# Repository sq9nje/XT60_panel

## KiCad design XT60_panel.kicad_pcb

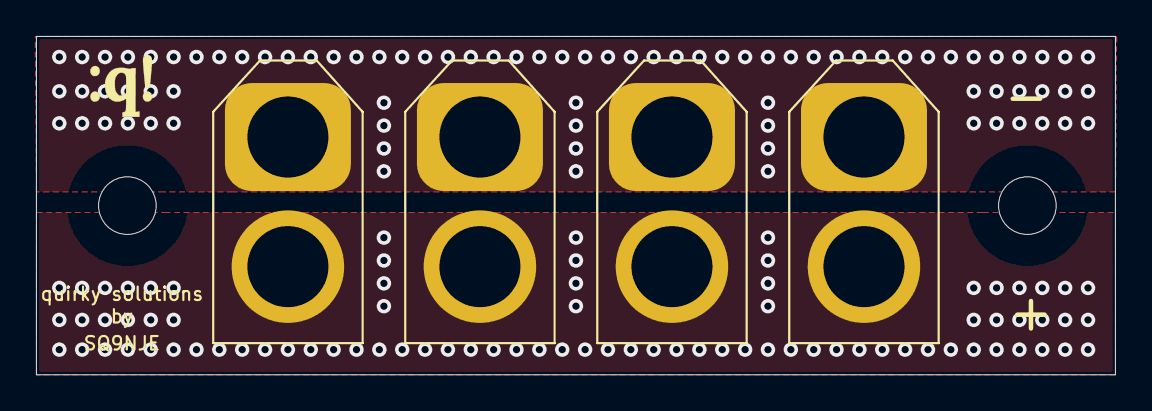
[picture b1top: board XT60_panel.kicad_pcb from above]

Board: 2 copper layers, 59.9 x 18.8 mm, 7 parts (0 on the bottom side), 2 nets, no tracks yet.

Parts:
H1, H2: MountingHole; MountingHole_3.2mm_M3
J1, J2, J3, J4: Conn_01x02; AMASS_XT60-F_1x02_P7.20mm_Vertical
Ref**: Val**; qs_logo

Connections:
unnamed: J1.1, J2.1, J3.1, J4.1
unnamed: J1.2, J2.2, J3.2, J4.2

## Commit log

2022-01-07 Let there be light
